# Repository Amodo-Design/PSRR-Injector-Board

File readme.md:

# PSRR Injector Board

Board to allow you to measure power supply rejection ratio.

Allows you to inject an AC ripple on top of your DC power supply to measure downstream. 0dB from 100Hz+. 

**[Product page](https://amodo-design.github.io/STAGING_AMODO_WEBSITE_SW/products/psrr-injector-board/)(https://amododesign.com/products/psrr-injector-board/)) · Designed by [Amodo](https://amododesign.com)**

## How it works

A clean lab supply connects on one side, and your DUT on the other. A function generator creates a signal that is AC-coupled onto the supply rail, superimposing a small ripple on top of the DC. Large series inductance (1000 µH) between the coupling node and the supply input forms an LC filter with the injection caps (880 µF per rail), keeping the supply clean and avoiding backfeed into the supply's regulation loop.

The circuit is mirrored so you can inject on either the positive or negative rail.

Note: the input impedance of your supply may be fairly low, so you may need a power amplifier between your function generator and the PSRR board. 

## Specifications

| Parameter | Value |
|---|---|
| Max voltage | ±30 V |
| Max current | 1 A |
| Injection capacitance | 880 µF per rail |
| Series inductance | 1000 µH per rail |
| Flat band | 100 Hz – 1 MHz+ |
| Low-frequency rolloff | 20 dB/dec below 100 Hz |
| Usable range | ~1 Hz (with calibration) |
| Supply input | 4 mm banana plugs |
| DUT output | 4 mm banana plugs |
| Signal injection | SMA |

## Repo layout

```
hardware/          KiCad project — schematic, PCB layout, 3D model
simulation/        LTSpice simulation file and component models
```

## Getting started

**PCB** — Open `hardware/AMODO_PSRR_INJECTOR_CBs_1.kicad_pro` in KiCad 6+.

**Simulation** — Open `simulation/psrr.asc` in LTSpice.

## License

Open-source hardware. Gerbers, schematics, and BOM are freely available — fabricate it yourself or send to your favourite PCB house.

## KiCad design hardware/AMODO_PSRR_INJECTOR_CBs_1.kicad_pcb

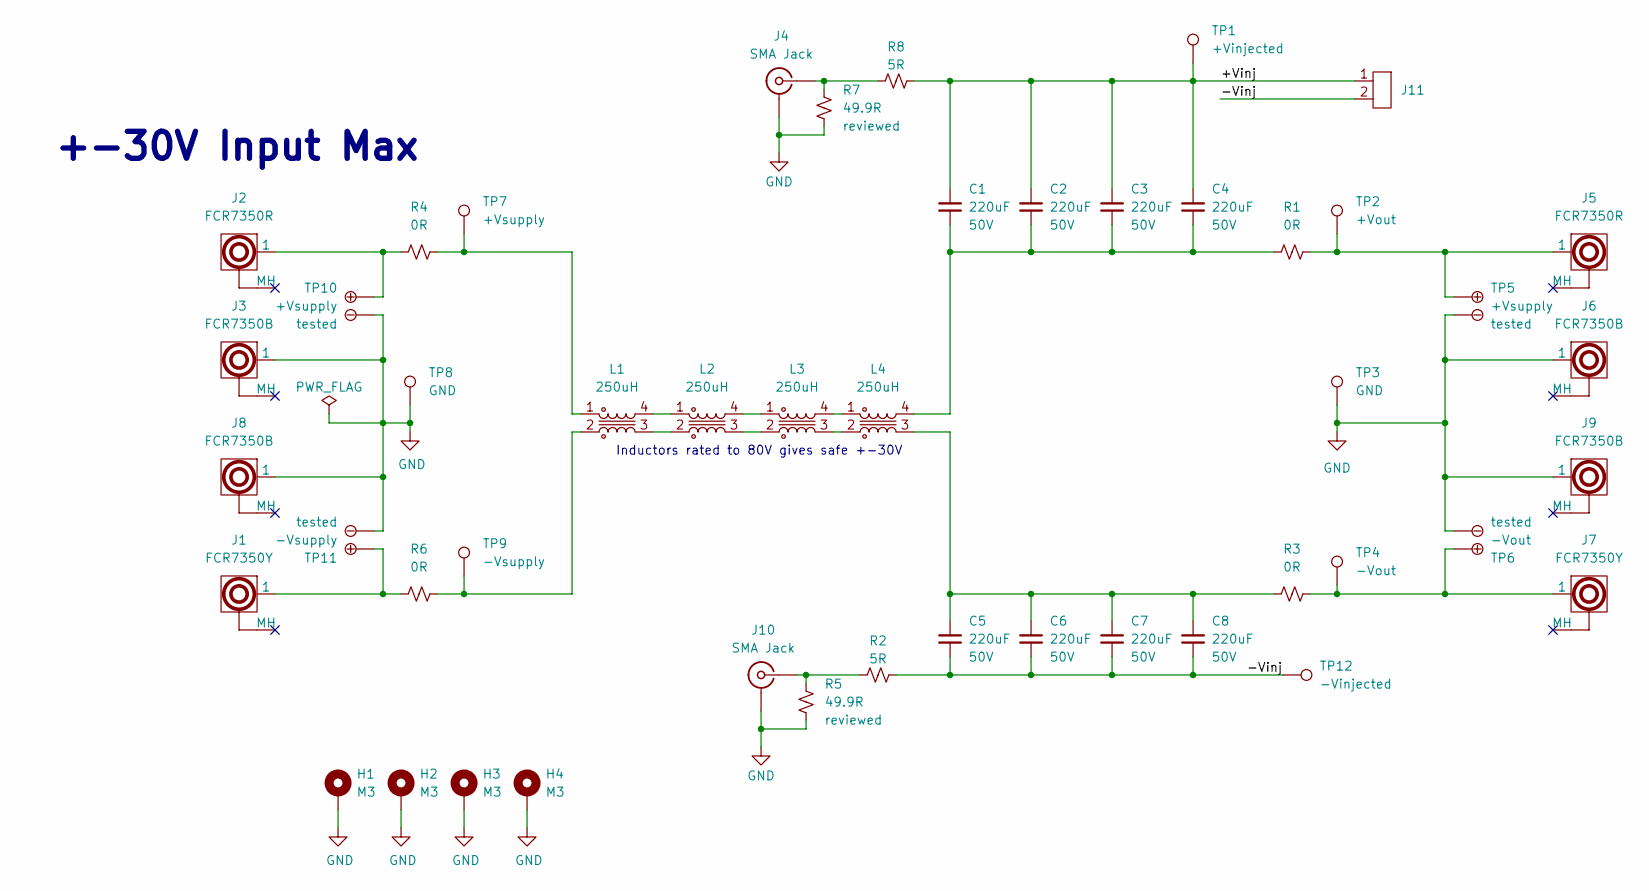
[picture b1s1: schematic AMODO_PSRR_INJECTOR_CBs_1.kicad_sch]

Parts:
C1, C2, C3, C4, C5, C6, C7, C8: 220uF; C_ALU_D12.5_L25_THT; Voltage 50V; mpn UEP1H221MHD
H1, H2, H3, H4: M3; MountingHole_3.2mm_M3_Pad
J1, J7: FCR7350Y; S16N-PC-YELLOW; mpn FCR7350Y
J2, J5: FCR7350R; S16N-PC-RED; mpn FCR7350R
J3, J6, J8, J9: FCR7350B; S16N-PC-BLACK; mpn FCR7350B
J4, J10: SMA Jack; SMA-J-P-H-ST-TH1; mpn SMA-J-P-H-ST-TH1
J11: 5-146252-1; mpn 5-146252-1|530153-2
L1, L2, L3, L4: 250uH; 744224; mpn 744224
R1, R3, R4, R6: 0R; R_1206_3216Metric; mpn RCC12060000Z0EA
R2, R8: 5R; R_0603_1608Metric; mpn CSRT0603FT5R00
R5, R7: 49.9R; R_0603_1608Metric; mpn ERJ-3EKF49R9V
TP1: +Vinjected; KeystoneMiniatureTestLoop; mpn 5002
TP2: +Vout; KeystoneMiniatureTestLoop; mpn 5002
TP3, TP8: GND; KeystoneMiniatureTestLoop; mpn 5002
TP4: -Vout; KeystoneMiniatureTestLoop; mpn 5002
TP5, TP10: +Vsupply; TestPoint_Dual_D1.5mm_H1.0mm
TP6: -Vout; TestPoint_Dual_D1.5mm_H1.0mm
TP7: +Vsupply; KeystoneMiniatureTestLoop; mpn 5002
TP9: -Vsupply; KeystoneMiniatureTestLoop; mpn 5002
TP11: -Vsupply; TestPoint_Dual_D1.5mm_H1.0mm
TP12: -Vinjected; KeystoneMiniatureTestLoop; mpn 5002

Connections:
/+Vinj: C1.1, C2.1, C3.1, C4.1, J11.1, R8.2, TP1.1
/-Vinj: C5.2, C6.2, C7.2, C8.2, J11.2, R2.2, TP12.1
GND: H1.1, H2.1, H3.1, H4.1, J3.1, J4.2 (Ext), J6.1, J8.1, J9.1, J10.2 (Ext), R5.2, R7.2, TP3.1, TP5.2, TP6.2, TP8.1, TP10.2, TP11.2
unnamed: C1.2, C2.2, C3.2, C4.2, L4.4, R1.1
unnamed: C5.1, C6.1, C7.1, C8.1, L4.3, R3.1
unnamed: J1.1, R6.1, TP11.1
unnamed: J2.1, R4.1, TP10.1
unnamed: J4.1 (In), R7.1, R8.1
unnamed: J5.1, R1.2, TP2.1, TP5.1
unnamed: J7.1, R3.2, TP4.1, TP6.1
unnamed: J10.1 (In), R2.1, R5.1
unnamed: L1.1, R4.2, TP7.1
unnamed: L1.2, R6.2, TP9.1
unnamed: L1.3, L2.2
unnamed: L1.4, L2.1
unnamed: L2.3, L3.2
unnamed: L2.4, L3.1
unnamed: L3.3, L4.2
unnamed: L3.4, L4.1

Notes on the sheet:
Inductors rated to 80V gives safe +-30V
+-30V Input Max

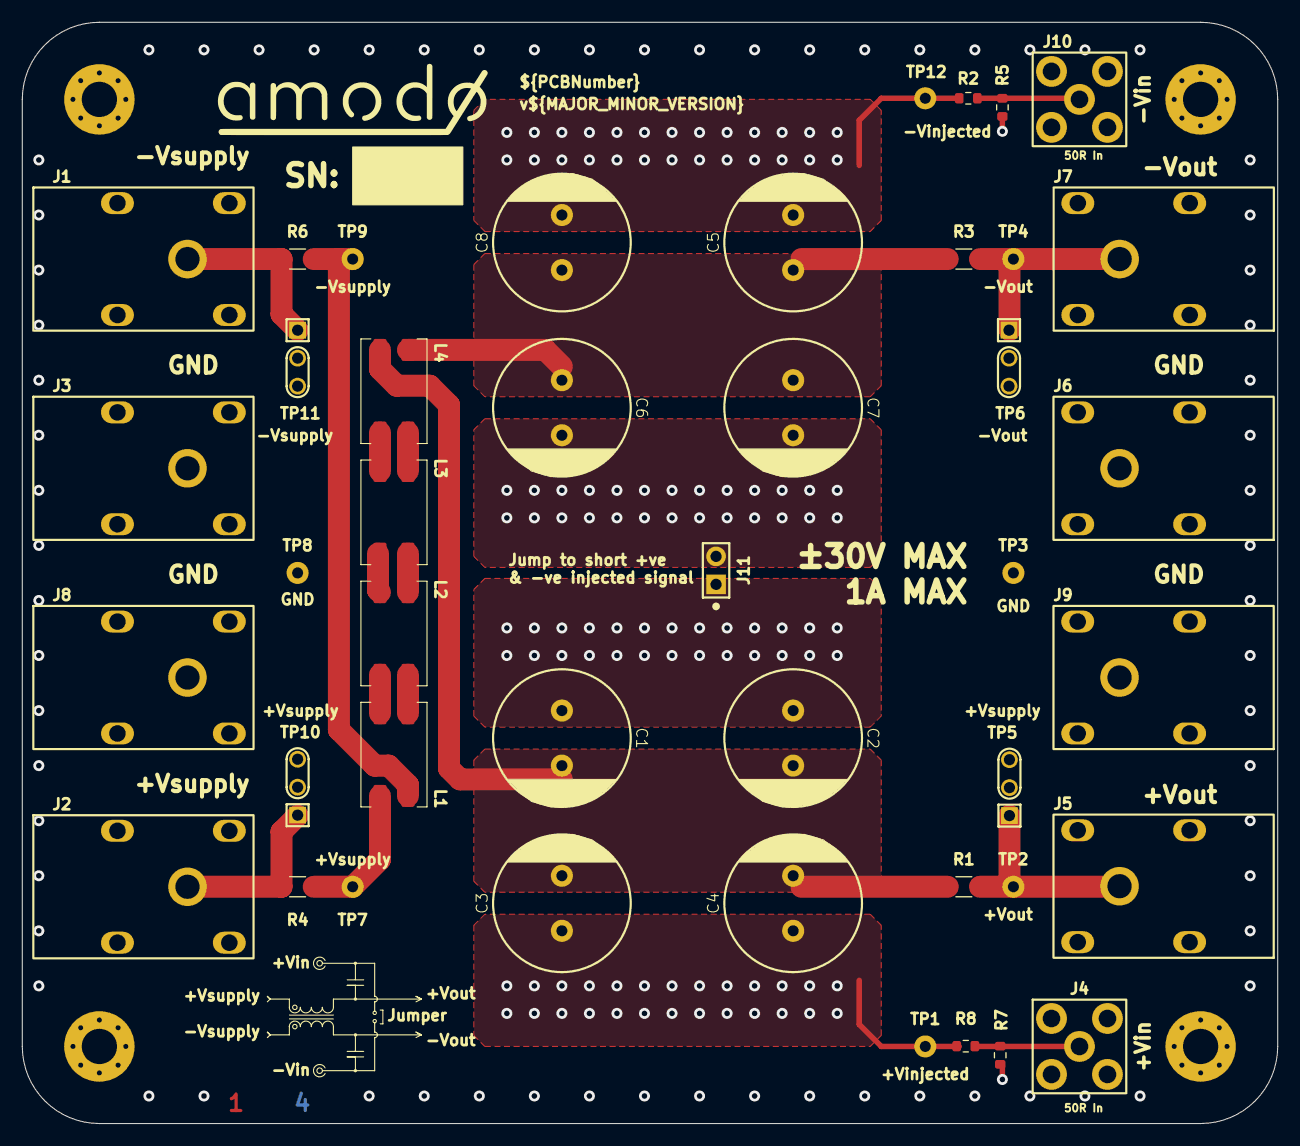
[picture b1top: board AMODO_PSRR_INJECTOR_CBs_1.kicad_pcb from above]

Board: 4 copper layers, 114.0 x 100.0 mm, 47 parts (0 on the bottom side), 19 nets.

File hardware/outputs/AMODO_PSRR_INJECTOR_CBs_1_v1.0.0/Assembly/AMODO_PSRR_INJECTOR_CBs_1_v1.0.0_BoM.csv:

"#","mpn","Description","Reference","Value","Footprint","Qty"
"1","5002","Test Point","TP1,TP2,TP3,TP4,TP7,TP8,TP9,TP12","+Vinjected,+Vout,+Vsupply,-Vinjected,-Vout,-Vsupply,GND","Amodo:KeystoneMiniatureTestLoop","8"
"2","UEP1H221MHD ","Electrolytic Capacitor, 220 µF, 50 V, ± 20%, Radial Leaded, 5000 hours @ 105°C, Bipolar","C1,C2,C3,C4,C5,C6,C7,C8","220uF","Amodo:C_ALU_D12.5_L25_THT","8"
"3","RCC12060000Z0EA","SMD Thick Film Resistor 0R 1206 5% 1W","R1,R3,R4,R6","0R","Amodo:R_1206_3216Metric","4"
"4","744224","SMD Power Inductor Differential Mode 2x250uH 1.2A 50%","L1,L2,L3,L4","250uH","Amodo:744224","4"
"5","FCR7350B","Banana socket, 4mm, shrouded, female, black , 24 A, 1 kV, THT","J3,J6,J8,J9","FCR7350B","Amodo:S16N-PC-BLACK","4"
"6","ERJ-3EKF49R9V","SMD Thick Film Resistor 49.9R 0603 1% 100mW","R5,R7","49.9R","Amodo:R_0603_1608Metric","2"
"7"," CSRT0603FT5R00","SMD Thick Film Resistor 5R 0603 1% 400mW","R2,R8","5R","Amodo:R_0603_1608Metric","2"
"8","SMA-J-P-H-ST-TH1","RF coaxial connector SMA THT Straight 50R 0-18GHz","J4,J10","SMA Jack","Amodo:SMA-J-P-H-ST-TH1","2"
"9","FCR7350R","Banana socket, 4mm, shrouded, female, red , 24 A, 1 kV, THT","J2,J5","FCR7350R","Amodo:S16N-PC-RED","2"
"10","FCR7350Y","Banana socket, 4mm, shrouded, female, yellow, 24 A, 1 kV, THT","J1,J7","FCR7350Y","Amodo:S16N-PC-YELLOW","2"
"11","5-146252-1|530153-2","2 Circuit 2.54mm pitch, Single Row, Straight, THT","J11","~","Amodo:5-146252-1","1"

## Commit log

2026-03-31 Changed license to CERN-OHL-P-2.0 and added gitignore
2026-03-31 Added design files and simulations
